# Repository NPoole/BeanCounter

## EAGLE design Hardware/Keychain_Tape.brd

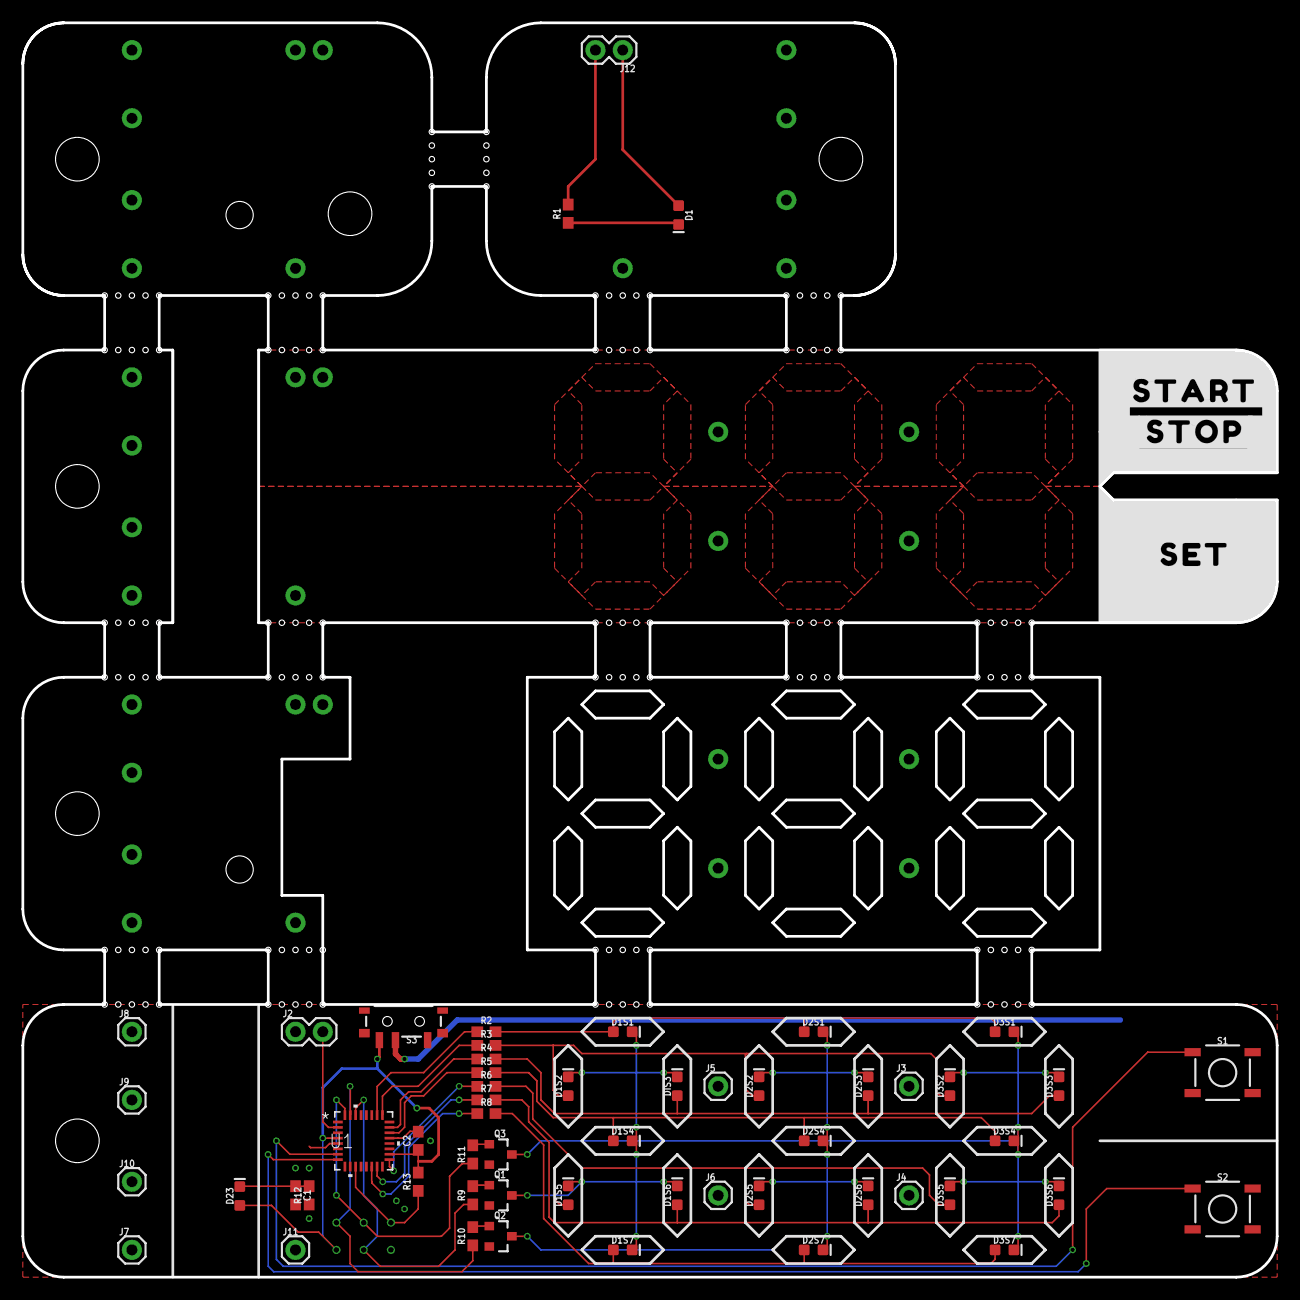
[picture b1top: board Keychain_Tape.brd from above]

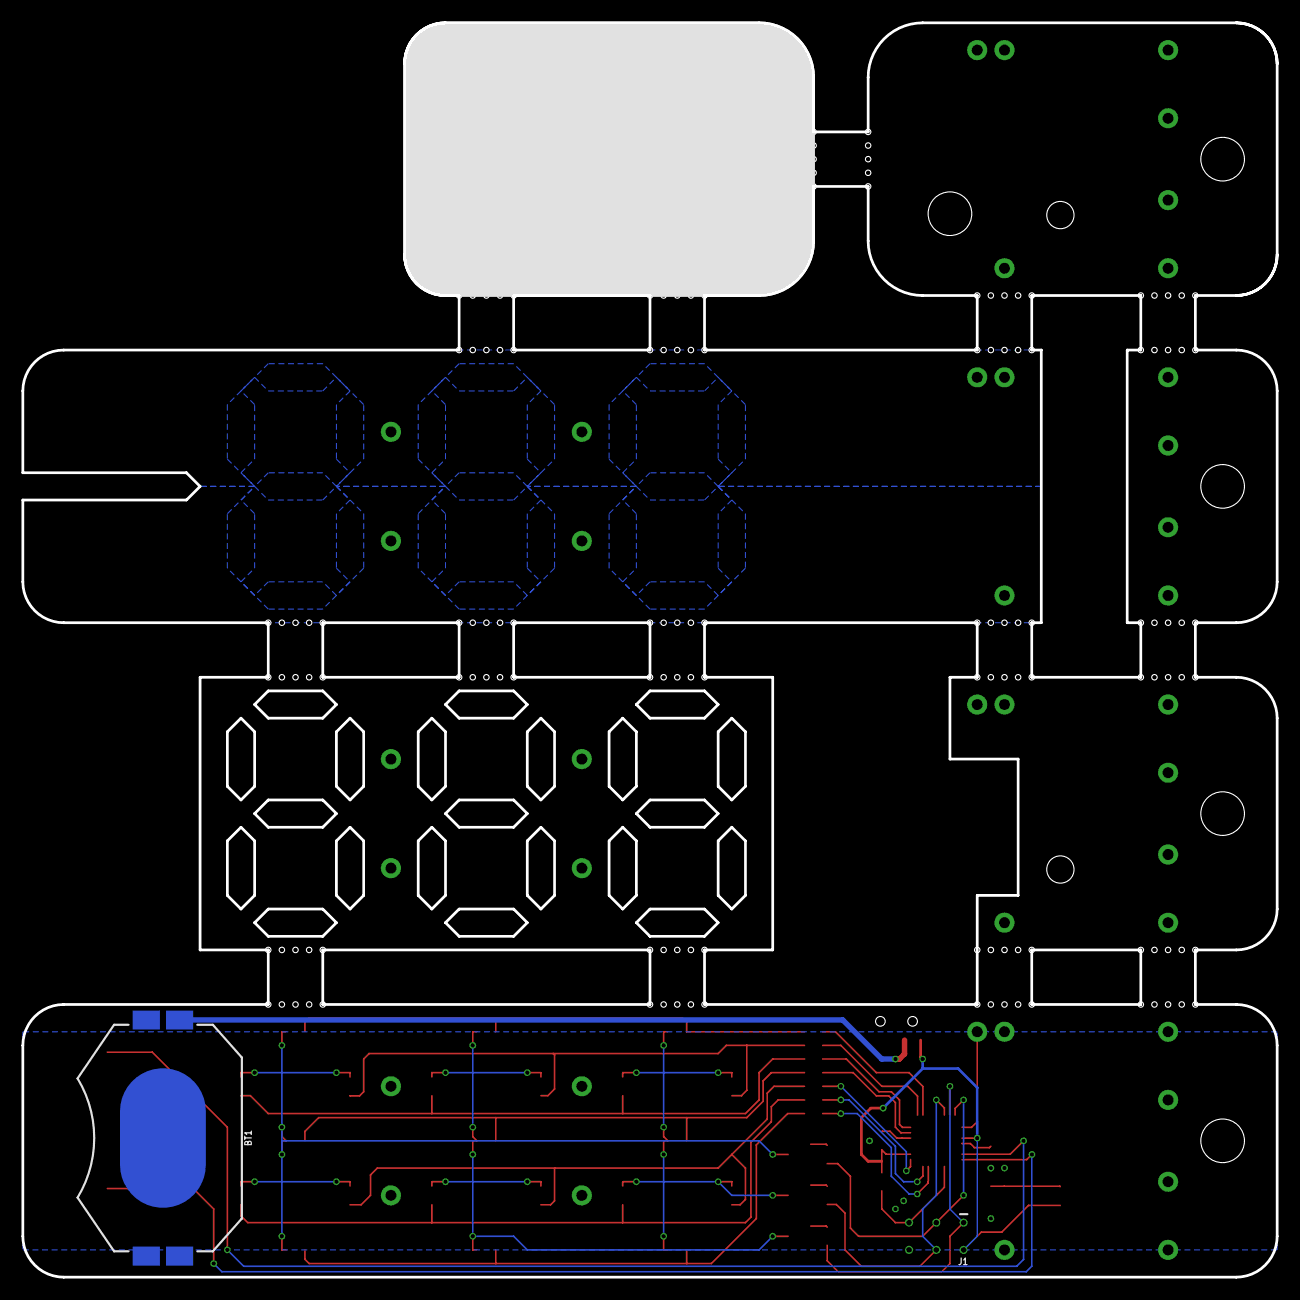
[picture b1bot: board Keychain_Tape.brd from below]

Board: 2 copper layers, 116.8 x 116.8 mm, 62 parts (2 on the bottom side), 34 nets.

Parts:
BT1: BATTCON_20MM_4LEGS_OVERPASTE_INNER
C1, C2: 0.1uF; 0603
D1: IR LED; LED-0603
D1S1, D1S2, D1S4, D1S5, D1S6, D1S7, D2S1, D2S2, D2S3, D2S4, D2S5, D2S6, D2S7, D3S1, D3S2, D3S3, D3S4, D3S5, D3S6, D3S7: LED-0603
D23: IR PHOTOTRANS; LED-0603
DIS3: LED-0603
FRAME1: FRAME-LETTER; CREATIVE_COMMONS
J1: AVR_SPI_PROG_3X2TESTPOINTS; 2X3_TEST_POINTS
J2, J12: 1X02
J3, J4, J5, J6, J7, J8, J9, J10, J11: 1X01
Q1, Q2, Q3: 220mA/50V/3.5Ω; SOT23-3
R1, R9, R10, R11, R12, R13: 1k; 0603
R2, R3, R4, R5, R6, R7, R8: 33; 0603
S1, S2: MOMENTARY-SWITCH-SPST-SMD-5.2MM-TALL; TACTILE_SWITCH_SMD_5.2MM
S3: SWITCH_SPST_SMD_A
U1: ATTINY861V-10MU; 32M1-A_ATM
U$1: #START#0
U$2: #STOP#0
U$3: #SET#0

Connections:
0: R2.1, U1.26
1: R3.1, U1.25
2: R4.1, U1.23
3: R5.1, U1.22
4: R6.1, U1.17
5: R7.1, U1.15
6: R8.1, U1.14
8/COPI: J1.4, R9.1, U1.30
9/CIPO: J1.1, R10.1, U1.31
10/SCK: J1.3, R11.1, U1.32
11: J2.2, U1.2
12: S1.1, U1.7
13: S2.1, U1.8
!RESET: J1.5, R13.1, U1.11
GND: BT1.2, C1.2, C2.2, J1.6, J2.1, Q1.2, Q2.2, Q3.2, R12.1, S1.3, S2.3, U1.5, U1.21
IR_DETECTOR: C1.1, D23.C, R12.2
unnamed: D1S1.C, D1S2.C, D1S4.C, D1S5.C, D1S6.C, D1S7.C, DIS3.C, Q1.3
unnamed: BT1.1, S3.2
unnamed: Q2.1, R10.2
unnamed: Q1.1, R9.2
unnamed: D2S1.C, D2S2.C, D2S3.C, D2S4.C, D2S5.C, D2S6.C, D2S7.C, Q2.3
unnamed: Q3.1, R11.2
unnamed: D3S1.C, D3S2.C, D3S3.C, D3S4.C, D3S5.C, D3S6.C, D3S7.C, Q3.3
unnamed: J12.2, R1.2
unnamed: D1.C, R1.1
unnamed: D1.A, J12.1
SEG1: D1S1.A, D2S1.A, D3S1.A, R2.2
SEG2: D1S2.A, D2S2.A, D3S2.A, R3.2
SEG3: D2S3.A, D3S3.A, DIS3.A, R4.2
SEG4: D1S4.A, D2S4.A, D3S4.A, R5.2
SEG5: D1S5.A, D2S5.A, D3S5.A, R6.2
SEG6: D1S6.A, D2S6.A, D3S6.A, R7.2
SEG7: D1S7.A, D2S7.A, D3S7.A, R8.2
V_BATT: C2.1, D23.A, J1.2, R13.2, S3.1, U1.4, U1.18

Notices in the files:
parts and their libraries:
SparkFun-Aesthetics: Licensing: Creative Commons ShareAlike 4.0 International - https://creativecommons.org/licenses/by-sa/4.0
SparkFun-Aesthetics: Released under the Creative Commons Attribution Share-Alike 4.0 License
SparkFun-Aesthetics: https://creativecommons.org/licenses/by-sa/4.0
